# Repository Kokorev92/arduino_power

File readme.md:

# DC/DC 5V converter for arduino
Designed in KiCad

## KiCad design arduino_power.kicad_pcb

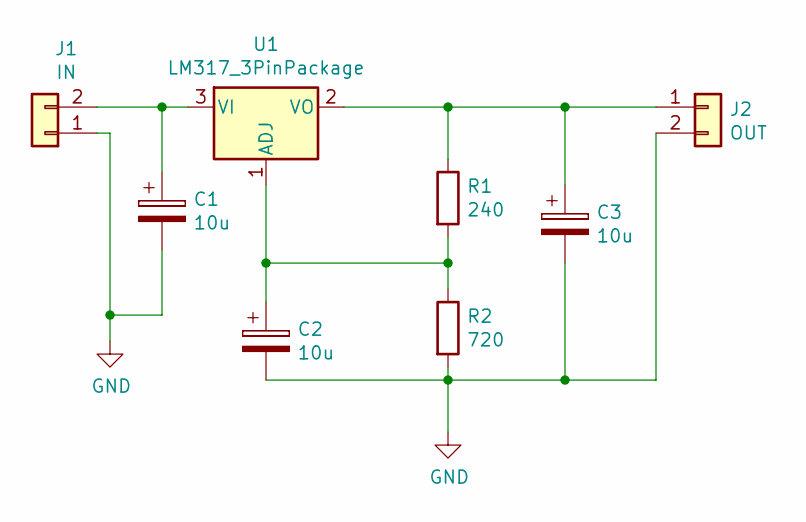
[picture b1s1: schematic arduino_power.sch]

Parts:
C1, C2, C3: 10u; CP_Radial_D5.0mm_P2.00mm
J1: IN; PinHeader_1x02_P2.54mm_Vertical
J2: OUT; PinHeader_1x02_P2.54mm_Vertical
R1: 240; R_Axial_DIN0309_L9.0mm_D3.2mm_P15.24mm_Horizontal
R2: 720; R_Axial_DIN0309_L9.0mm_D3.2mm_P15.24mm_Horizontal
U1: LM317_3PinPackage; TO-220-3_Vertical

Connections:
GND: C1.2, C2.2, C3.2, J1.1, J2.2, R2.2
unnamed: C1.1, J1.2, U1.3 (VI)
unnamed: C2.1, R1.2, R2.1, U1.1 (ADJ)
unnamed: C3.1, J2.1, R1.1, U1.2 (VO)

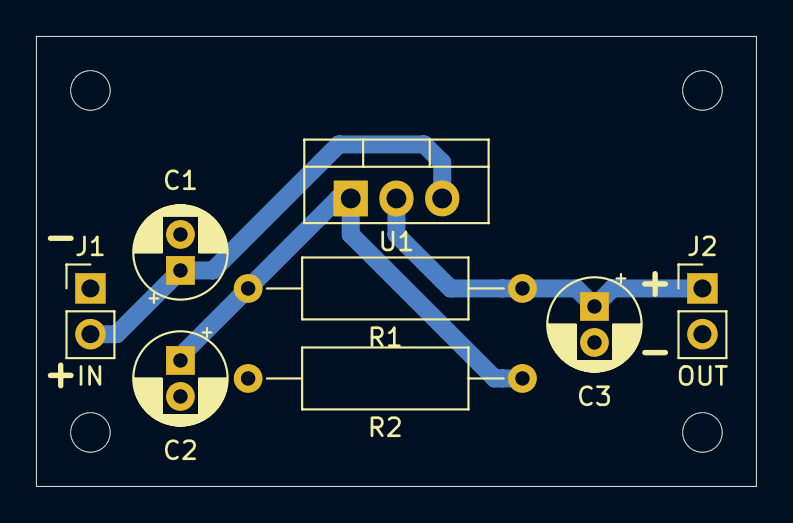
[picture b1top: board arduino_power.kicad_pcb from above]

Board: 2 copper layers, 40.0 x 25.0 mm, 9 parts (0 on the bottom side), 4 nets.

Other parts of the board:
REF1: MountingHole_2.2mm_M2

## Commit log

2020-02-29 Init git
2020-02-29 add readme
